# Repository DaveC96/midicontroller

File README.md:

# midicontroller

Another project for me to start and probably get bored of half way through!
I guess it's basically a LaunchControl XL, or a bit of the SL MkIII.

- 8 push encoders
- 8 OLEDs
- 8 layers of MIDI CC mappings
- MIDI over USB
- Config from desktop control software via SysEx
-

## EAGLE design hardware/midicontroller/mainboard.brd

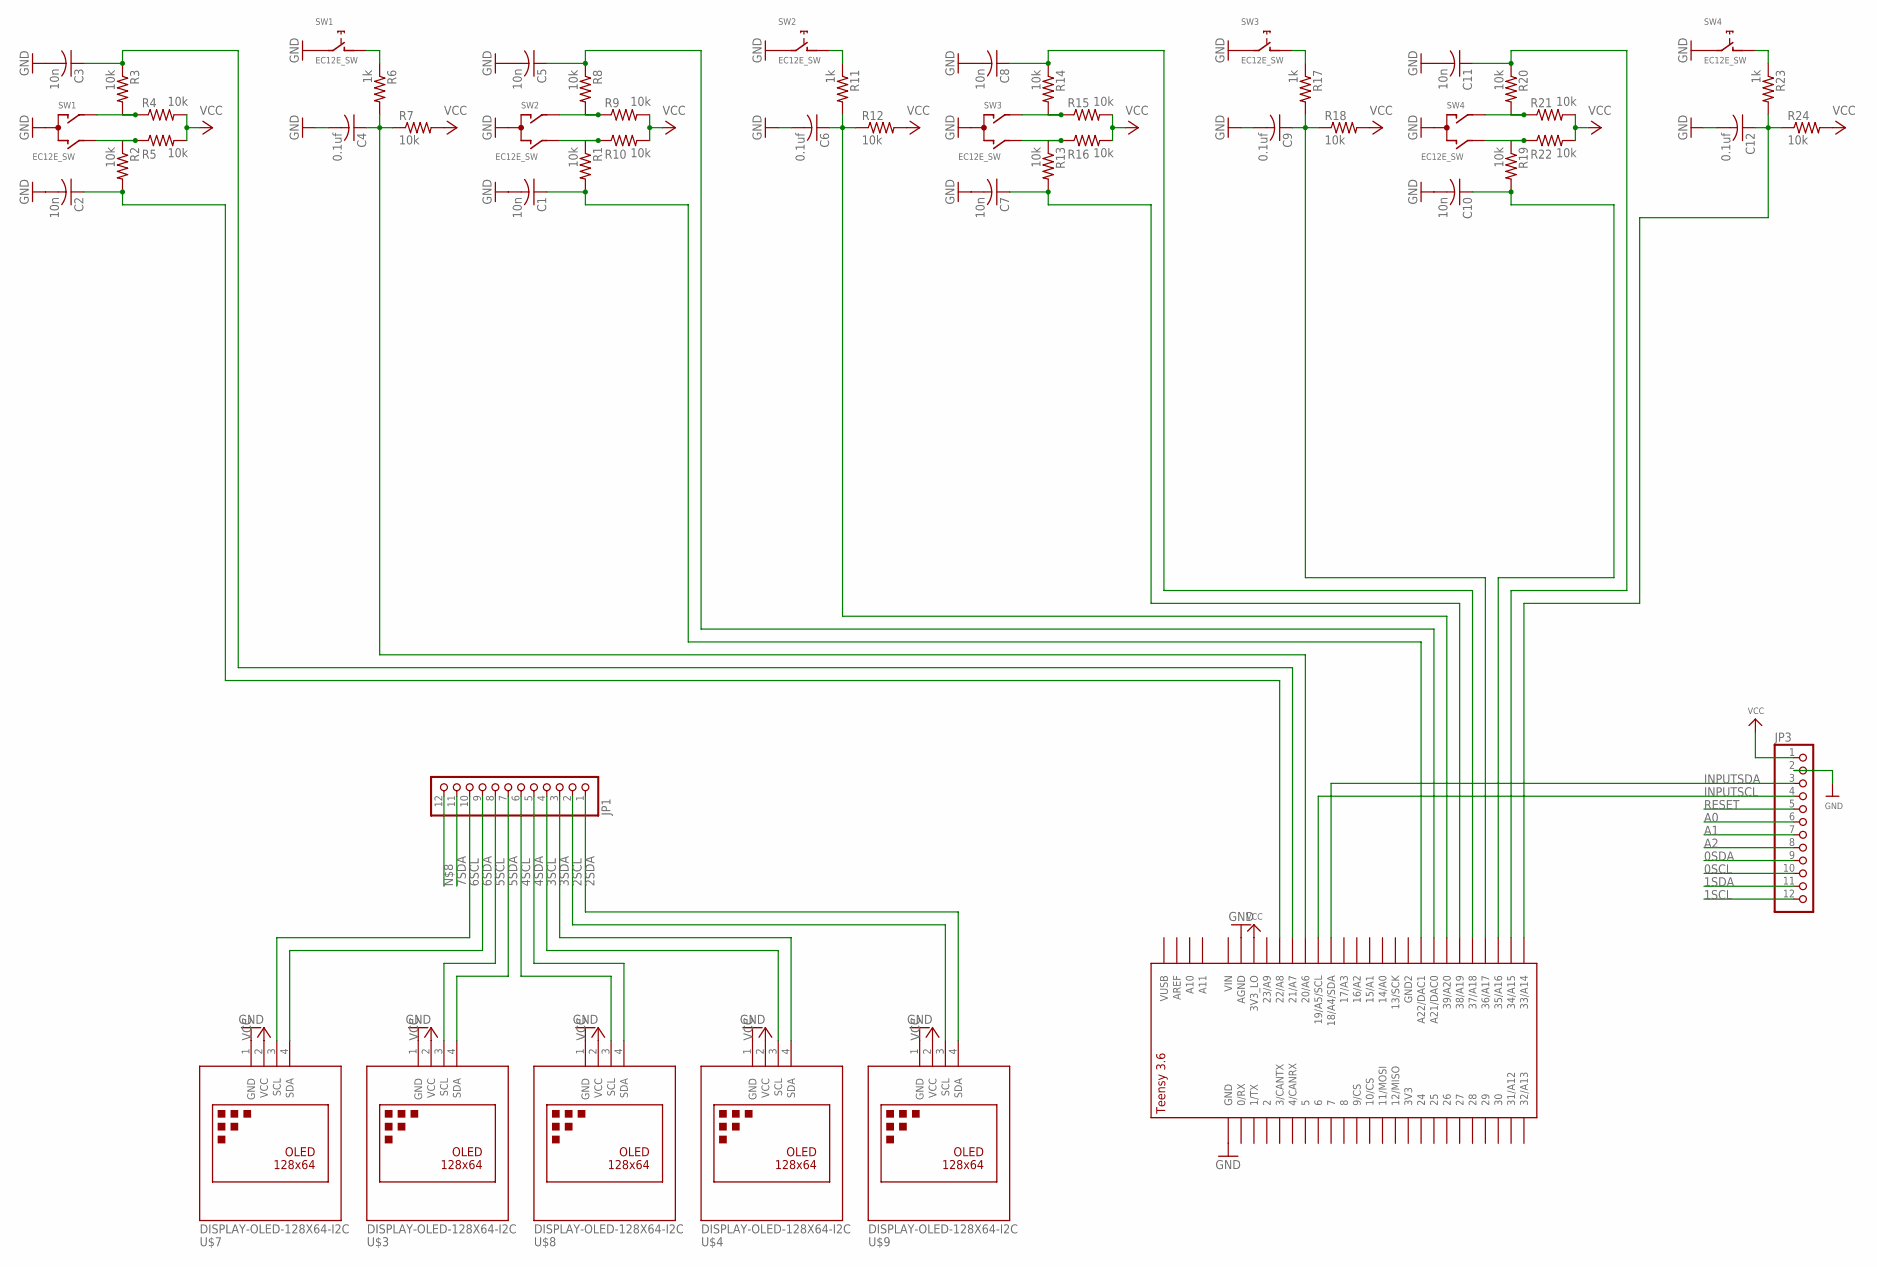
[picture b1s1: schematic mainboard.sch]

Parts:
C1, C2, C3, C5, C7, C8, C10, C11: 10n; C050-025X075
C4, C6, C9, C12: 0.1uf; C050-025X075
JP1, JP3: HEADER-1X12; 1X12_ROUND
R1, R2, R3, R4, R5, R7, R8, R9, R10, R12, R13, R14, R15, R16, R18, R19, R20, R21, R22, R24: 10k; 0207/9
R6, R11, R17, R23: 1k; 0207/9
SW1, SW2, SW3, SW4: EC12E_SW; ALPS_EC12E_SW
U$1: TEENSY_3.5/3.6_BASIC
U$3, U$4, U$7, U$8, U$9: DISPLAY-OLED-128X64-I2C

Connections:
0SCL: JP3.10
0SDA: JP3.9
1SCL: JP3.12
1SDA: JP3.11
2SCL: JP1.2, U$9.3 (SCL)
2SDA: JP1.1, U$9.4 (SDA)
3SCL: JP1.4, U$4.3 (SCL)
3SDA: JP1.3, U$4.4 (SDA)
4SCL: JP1.6, U$8.3 (SCL)
4SDA: JP1.5, U$8.4 (SDA)
5SCL: JP1.8, U$3.3 (SCL)
5SDA: JP1.7, U$3.4 (SDA)
6SCL: JP1.10, U$7.3 (SCL)
6SDA: JP1.9, U$7.4 (SDA)
7SDA: JP1.11
A0: JP3.6
A1: JP3.7
A2: JP3.8
GND: C1.2, C2.2, C3.2, C4.2, C5.2, C6.2, C7.2, C8.2, C9.2, C10.2, C11.2, C12.2, JP3.2, SW1.C, SW1.E (2), SW2.C, SW2.E (2), SW3.C, SW3.E (2), SW4.C, SW4.E (2), U$1.AGND, U$1.GND, U$3.1 (GND), U$4.1 (GND), U$7.1 (GND), U$8.1 (GND), U$9.1 (GND)
INPUTSCL: JP3.4, U$1.19/A5/SCL
INPUTSDA: JP3.3, U$1.18/A4/SDA
unnamed: R2.1, R5.1, SW1.B
unnamed: R3.2, R4.1, SW1.A
unnamed: C2.1, R2.2, U$1.22/A8
unnamed: R6.1, SW1.D (1)
unnamed: C3.1, R3.1, U$1.21/A7
unnamed: C4.1, R6.2, R7.1, U$1.20/A6
unnamed: R1.1, R10.1, SW2.B
unnamed: R8.2, R9.1, SW2.A
unnamed: C1.1, R1.2, U$1.A22/DAC1
unnamed: C5.1, R8.1, U$1.21/DAC0 (A21/DAC0)
unnamed: R11.1, SW2.D (1)
unnamed: C6.1, R11.2, R12.1, U$1.39/A20
unnamed: R13.1, R16.1, SW3.B
unnamed: R14.2, R15.1, SW3.A
unnamed: C7.1, R13.2, U$1.38/A19
unnamed: C8.1, R14.1, U$1.37/A18
unnamed: R17.1, SW3.D (1)
unnamed: C9.1, R17.2, R18.1, U$1.36/A17
unnamed: R19.1, R22.1, SW4.B
unnamed: R20.2, R21.1, SW4.A
unnamed: C10.1, R19.2, U$1.35/A16
unnamed: C11.1, R20.1, U$1.34/A15
unnamed: R23.1, SW4.D (1)
unnamed: C12.1, R23.2, R24.1, U$1.33/A14
RESET: JP3.5
VCC: JP3.1, R4.2, R5.2, R7.2, R9.2, R10.2, R12.2, R15.2, R16.2, R18.2, R21.2, R22.2, R24.2, U$1.3V3_LO, U$3.2 (VCC), U$4.2 (VCC), U$7.2 (VCC), U$8.2 (VCC), U$9.2 (VCC)

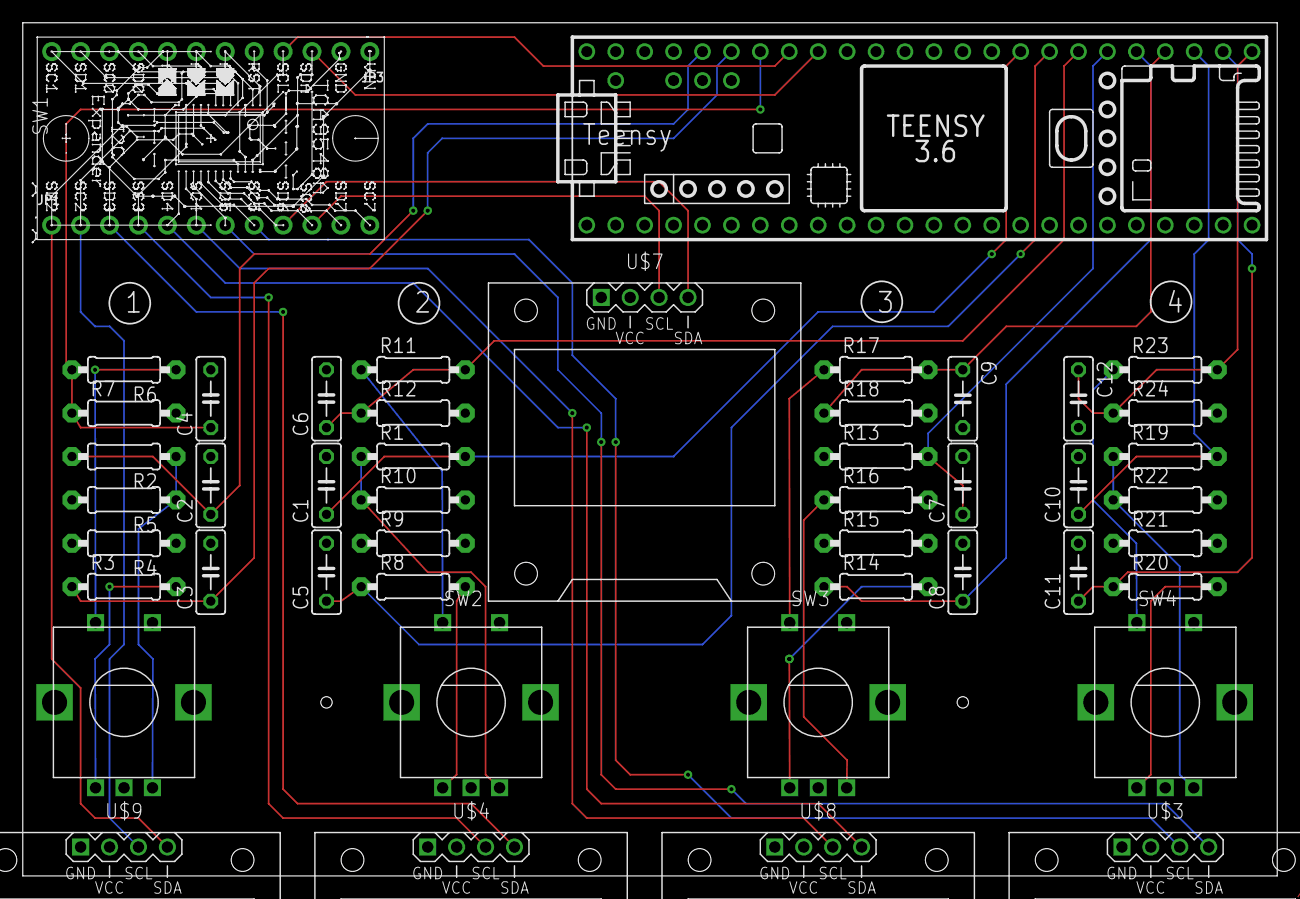
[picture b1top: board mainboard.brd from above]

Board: 2 copper layers, 110.2 x 74.9 mm, 48 parts (0 on the bottom side), 38 nets.

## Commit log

2020-07-01 Wireframe UI for control software
2020-07-01 Forgot gitignore and readme
2020-07-01 Platformio setup for device firmware
2020-07-01 Tidying up to call it a night
2020-07-02 Control software model and layering scheme
2020-07-04 Starting on hardware
2020-07-04 First prototype board design
2020-07-05 getting to grips with sysex on teensy...
2020-07-05 UI plumbing
2020-07-05 sysex transfer spec first draft
2020-07-06 First pass sysex comms
2020-07-06 Changed sysex stuff so it actually works
2020-07-06 changed controller model into class
2020-07-06 absolute abomination attempt at serialisation
2020-07-06 let's not talk about this
2020-07-07 Better serialisation & started bringing up rtmidi
2020-07-08 Disgusting firmware having fun with the new displays. Also start on decoding sysex.
2020-07-09 deserialise in model, causes crash atm...
2020-07-09 deserialise in model, assignments now crash
2020-07-27 Starting to test the PCB
2020-07-28 Hardware bringup pt. 1
2020-07-31 Encoders now alive
2020-07-31 Getting ahead of myself messing with UI
2020-08-01 Starting on some architecture I guess
2020-08-01 Moved to different encoder approach. Maybe use that for buttons too? TODO.
2020-08-08 Starting to move the scaffolding code into a proper architecture
2020-08-08 ...Now with a working link
2020-08-08 Move headers to include/
2020-08-08 Session UI reads from model
2020-08-08 Speculative model transfer
2020-08-21 Changed pin assignments for v2 proto

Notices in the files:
parts and their libraries:
diy-modules: Released under the Creative Commons Attribution 4.0 International License: http://creativecommons.org/licenses/by/4.0
microbuilder: This work is placed in the public domain, and may be freely used for commercial and non-commercial work with the following conditions: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
